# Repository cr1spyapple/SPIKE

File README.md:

# SPIKE
A sleek and speedy ESP32-S3 powered development board

Designed in KiCAD as part of STASIS for Hack Club. I took up this project to learn more about PCB and MCU design. This acts as a prototype of sorts to my e-Reader project <a href="https://github.com/cr1spyapple/Bebop">"Bebop"</a> which will use similar hardware to this.

## Specs:
- 32 GPIO pins
- 16MB flash
- 8MB PSRAM
- WiFi and Bluetooth connectivity
- USB-C port

## PCB Model

## Schematic

## PCB Traces

## Bill of Materials

|Name                                                                                                       |Purpose                   |Quantity|Total Cost (USD)|Link                                                                                                         |Distributor|
|-----------------------------------------------------------------------------------------------------------|--------------------------|--------|----------------|-------------------------------------------------------------------------------------------------------------|-----------|
|10kΩ ±5% 100mW 0603 Thick Film Resistor                                                                    |                          |100     |0.11            |https://www.lcsc.com/product-detail/C2930027.html                                                            |           |
|1.2pF 50V Ceramic Capacitor C0G 0402                                                                       |                          |50      |1.79            |https://www.lcsc.com/product-detail/C76899.html                                                              |           |
|100nF ±10% 16V Ceramic Capacitor X7R 0402                                                                  |                          |100     |0.16            |https://www.lcsc.com/product-detail/C60474.html                                                              |           |
|1uF ±10% 16V Ceramic Capacitor X5R 0402                                                                    |                          |100     |0.38            |https://www.lcsc.com/product-detail/C29266.html                                                              |           |
|20pF ±5% 50V Ceramic Capacitor C0G 0402                                                                    |                          |100     |0.57            |https://www.lcsc.com/product-detail/C76959.html                                                              |           |
|2.7V~3.6V 128Mbit 133MHz SPI SOIC-8-208mil Memory (ICs) RoHS                                               |                          |3       |7.92            |https://www.lcsc.com/product-detail/C97521.html                                                              |           |
|2A 1uH ±20% 95mΩ 3.1A 0805 Fixed Inductors RoHS                                                            |                          |5       |1.05            |https://www.lcsc.com/product-detail/C1331798.html                                                            |           |
|140mA 24nH ±3% 2.3Ω Thick Film Inductor 0201 Fixed Inductors RoHS                                          |                          |100     |0.84            |https://www.lcsc.com/product-detail/C206441.html                                                             |           |
|500mA 2nH 100mΩ 0603 Fixed Inductors RoHS                                                                  |                          |50      |0.65            |https://www.lcsc.com/product-detail/C395081.html                                                             |           |
|USB-C (USB TYPE-C) Receptacle Connector 16 Position Surface Mount                                          |                          |5       |0.94            |https://www.lcsc.com/product-detail/C165948.html                                                             |           |
|Red 645nm LED Indication - Discrete 2.4V 0603                                                              |                          |100     |0.70            |https://www.lcsc.com/product-detail/C2286.html                                                               |           |
|22uF ±20% 10V Ceramic Capacitor X5R 0603                                                                   |                          |10      |0.21            |https://www.lcsc.com/product-detail/C86295.html                                                              |           |
|10nF ±10% 50V Ceramic Capacitor X7R 0603                                                                   |                          |100     |0.37            |https://www.lcsc.com/product-detail/C100042.html                                                             |           |
|499Ω ±1% 62.5mW 0402 Thick Film Resistor                                                                   |                          |100     |0.07            |https://www.lcsc.com/product-detail/C4125.html                                                               |           |
|800mA 2.4nH 80mΩ Multilayer inductor 0402 Fixed Inductors RoHS                                             |                          |10      |0.10            |https://www.lcsc.com/product-detail/C275281.html                                                             |           |
|10uF ±20% 25V Ceramic Capacitor X5R 0603                                                                   |                          |20      |0.61            |https://www.lcsc.com/product-detail/C96446.html                                                              |           |
|Crystal 40MHz ±10ppm 15pF SMD3225-4P                                                                       |                          |10      |0.69            |https://www.lcsc.com/product-detail/C5444549.html                                                            |           |
|SOP-8L Memory (ICs) RoHS                                                                                   |                          |2       |8.93            |https://www.lcsc.com/product-detail/C3028887.html                                                            |           |
|1.5MHz Step-down type Adjustable 600mV~5.5V 2A SOT-563 Voltage Regulators - DC DC Switching Regulators RoHS|                          |5       |0.59            |https://www.lcsc.com/product-detail/C163217.html                                                             |           |
|-98.4dBm 150Mbps 2.412GHz~2.484GHz 2.4GHz 3V~3.6V QFN-56-EP(7x7) RF Transceiver ICs RoHS                   |                          |3       |9.06            |https://www.lcsc.com/product-detail/C2913192.html                                                            |           |
|Tactile Switch SPST 160gf 2mm SMD (SMT) Tab 4mm x 3mm Surface Mount                                        |                          |10      |0.57            |https://www.lcsc.com/product-detail/C720477.html                                                             |           |
|100mW 100kΩ 75V Thick Film Resistor ±100ppm/℃ ±1% 0603 Chip Resistor - Surface Mount RoHS                  |                          |100     |0.15            |https://www.lcsc.com/product-detail/C14675.html                                                              |           |
|453kΩ ±0.1% 100mW 0603 Thin Film Resistor                                                                  |                          |20      |0.48            |https://www.lcsc.com/product-detail/C2686428.html                                                            |           |
|75Ω ±1% 100mW 0603 Thick Film Resistor                                                                     |                          |100     |0.19            |https://www.lcsc.com/product-detail/C4275.html                                                               |           |
|22Ω ±5% 100mW 0603 Thick Film Resistor                                                                     |                          |100     |0.12            |https://www.lcsc.com/product-detail/C2907129.html                                                            |           |
|5.1kΩ ±1% 100mW 0603 Thick Film Resistor                                                                   |                          |100     |0.13            |https://www.lcsc.com/product-detail/C2907044.html                                                            |           |
|0Ω 125mW 200V Thick Film Resistor 0805 Chip Resistor - Surface Mount RoHS                                  |                          |100     |0.63            |https://www.lcsc.com/product-detail/C844934.html                                                             |           |
|4.7uF ±10% 16V Ceramic Capacitor X5R 0603                                                                  |                          |10      |0.14            |https://www.lcsc.com/product-detail/C19666.html                                                              |           |
|Header pins                                                                                                |Header pins for PCB       |1       |1.98            |https://www.aliexpress.com/item/1005008703085861.html?search_p4p_id=202605091107184238603551627500001818552_9|Aliexpress |
|Soldering paste (20g)                                                                                      |Soldering components      |1       |3.46            |https://www.aliexpress.com/item/1005009377104599.html?mp=1                                                   |Aliexpress |
|Hot Plate                                                                                                  |Soldering SMD components  |1       |13.99           |https://www.aliexpress.com/item/1005007016135854.html?mp=1                                                   |Aliexpress |
|65W Type-C power adapter                                                                                   |Power supply for Hot Plate|1       |12.68           |https://www.ebay.co.uk/itm/406309629830                                                                      |Ebay       |
|PCB                                                                                                        |PCB                       |5       |4.10            |                                                                                                             |JLCPCB     |

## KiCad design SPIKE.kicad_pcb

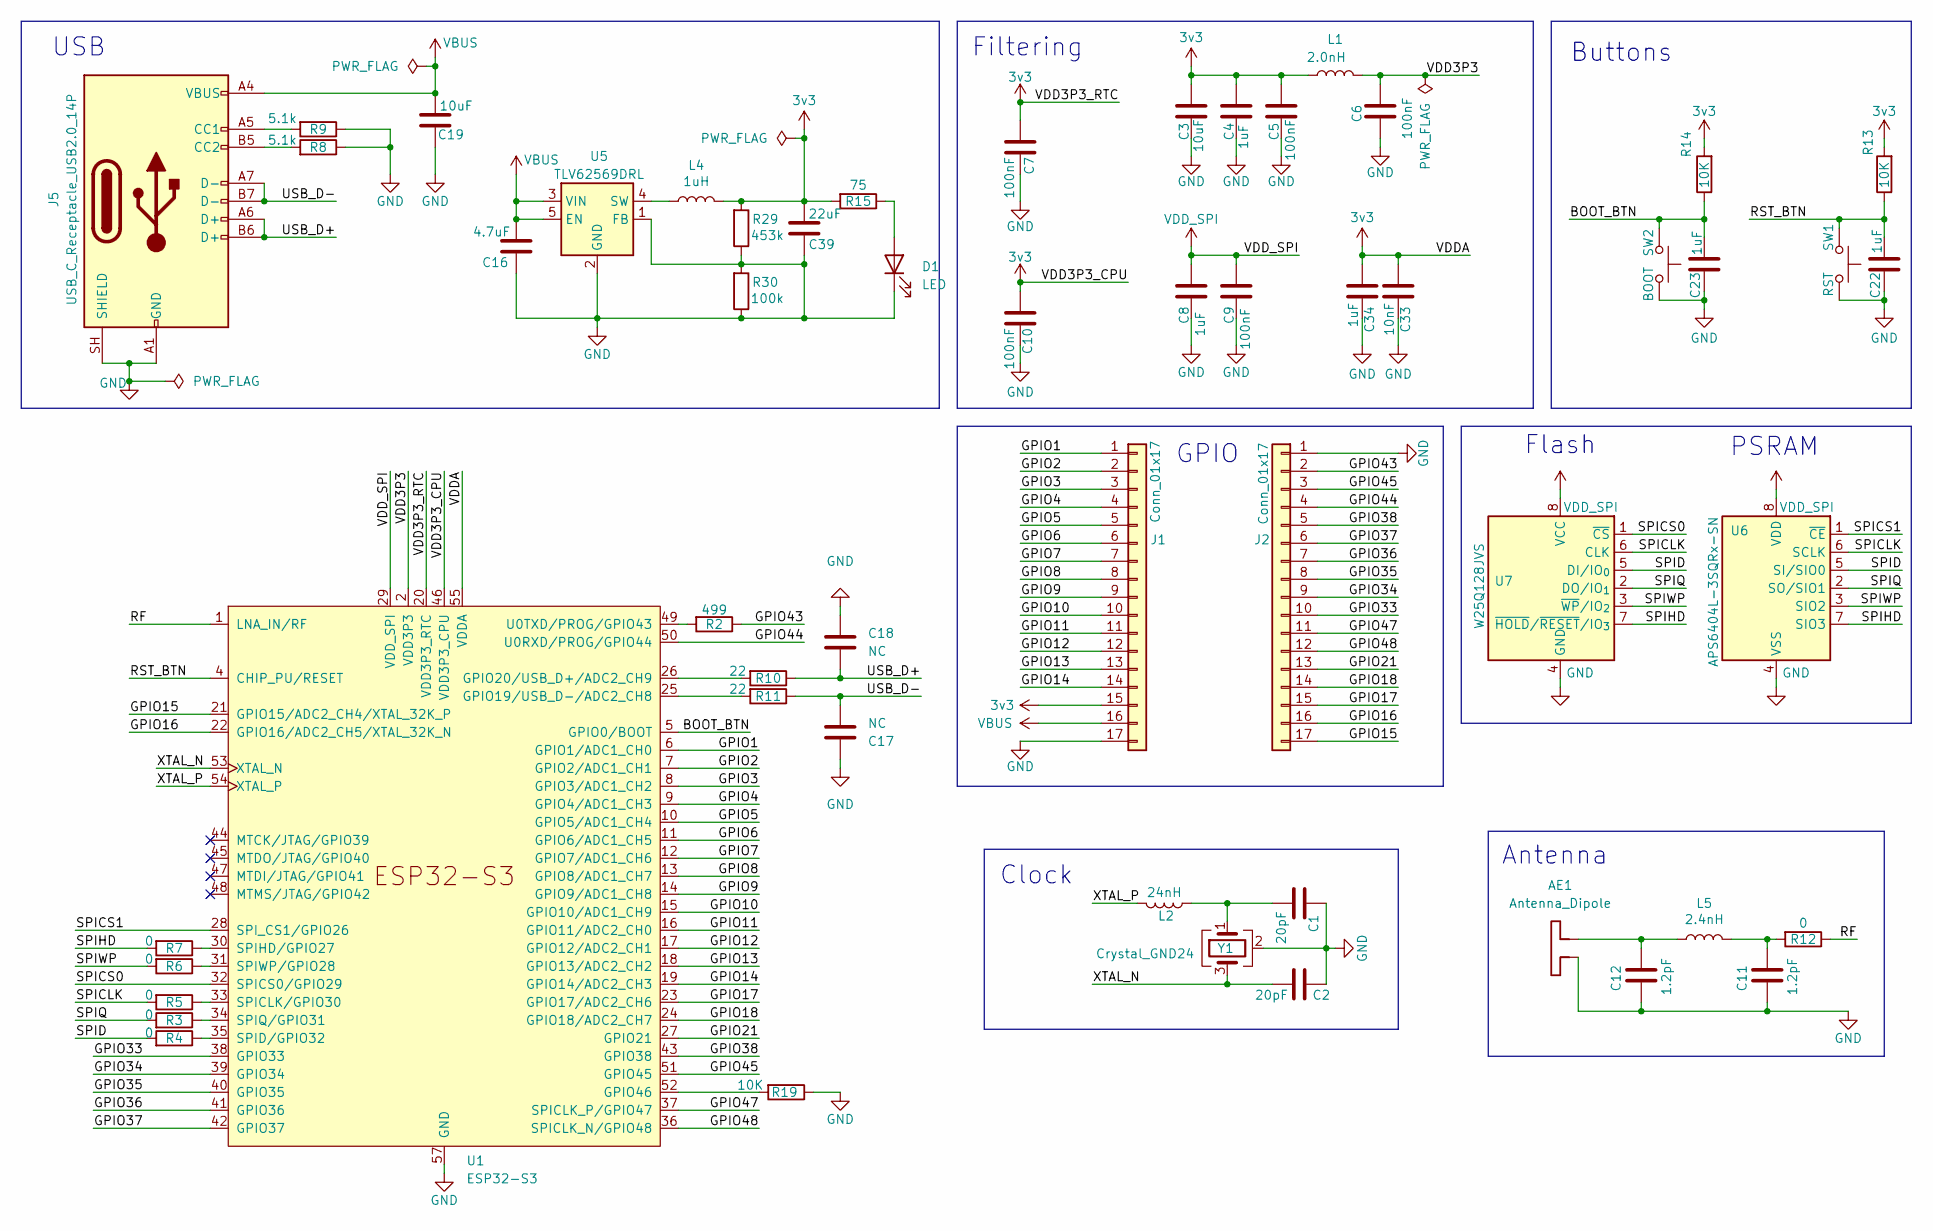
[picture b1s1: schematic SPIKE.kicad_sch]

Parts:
AE1: Antenna_Dipole; Trace Antenna 2.4GHz
C1, C2: 20pF; C_0402_1005Metric; MNF PART NUMBER C1554
C3, C19: 10uF; C_0603_1608Metric; MNF PART NUMBER C19702
C4, C8, C22, C23, C34: 1uF; C_0402_1005Metric; MNF PART NUMBER C52923
C5, C6, C7, C9, C10: 100nF; C_0402_1005Metric; MNF PART NUMBER C1591
C11, C12: 1.2pF; C_0402_1005Metric; MNF PART NUMBER C52923
C16: 4.7uF; C_0603_1608Metric; MNF PART NUMBER C19702
C17, C18: NC; R_0805_2012Metric
C33: 10nF; C_0603_1608Metric; MNF PART NUMBER C57112
C39: 22uF; C_0603_1608Metric; MNF PART NUMBER C19702
D1: LED; LED_0603_1608Metric; MFN PART NUMBER C2286
J1, J2: Conn_01x17; PinHeader_1x17_P2.54mm_Vertical
J5: USB_C_Receptacle_USB2.0_14P; USB_C_Receptacle_HRO_TYPE-C-31-M-12; MNF PART NUMBER C165948
L1: 2.0nH; L_0603_1608Metric; MNF PART NUMBER C370234
L2: 24nH; L_0201_0603Metric; MNF PART NUMBER C139271
L4: 1uH; L_0805_2012Metric; MNF PART NUMBER C19533
L5: 2.4nH; L_0805_2012Metric; MNF PART NUMBER C19533
R2: 499; R_0805_2012Metric; MNF PART NUMBER C17722
R3, R4, R5, R6, R7, R12: 0; R_0805_2012Metric; MNF PART NUMBER C17477
R8, R9: 5.1k; R_0603_1608Metric; MNF PART NUMBER C23186
R10, R11: 22; R_0603_1608Metric; MNF PART NUMBER C23345
R13, R14, R19: 10K; R_0603_1608Metric; MNF PART NUMBER C25804
R15: 75; R_0603_1608Metric; MNF PART NUMBER C4275
R29: 453k; R_0603_1608Metric; MNF PART NUMBER C101055
R30: 100k; R_0603_1608Metric; MNF PART NUMBER C25803
SW1: RST; SW_Push_SPST_NO_Alps_SKRK; MNF PART NUMBER C720477
SW2: BOOT; SW_Push_SPST_NO_Alps_SKRK; MNF PART NUMBER C720477
U1: ESP32-S3; QFN-56-1EP_7x7mm_P0.4mm_EP5.6x5.6mm; MNF PART NUMBER C2913192
U5: TLV62569DRL; SOT-563; MNF PART NUMBER C163217
U6: APS6404L-3SQRx-SN; SOIC-8_3.9x4.9mm_P1.27mm; MNF PART NUMBER C5333729
U7: W25Q128JVS; SOIC-8_5.3x5.3mm_P1.27mm; MNF PART NUMBER C97521
Y1: Crystal_GND24; Crystal_SMD_3225-4Pin_3.2x2.5mm; MNF PART NUMBER C9010

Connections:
3v3: C3.2, C4.2, C5.2, C7.2, C10.2, C33.2, C34.2, C39.2, J1.15, L1.1, L4.1, R13.2, R14.2, R15.2, R29.2, U1.20 (VDD3P3_RTC), U1.46 (VDD3P3_CPU), U1.55 (VDDA), U1.56 (VDDA)
/BOOT_BTN: C23.2, R14.1, SW2.1, U1.5 (GPIO0/BOOT)
/GPIO1: J1.1, U1.6 (GPIO1/ADC1_CH0)
/GPIO2: J1.2, U1.7 (GPIO2/ADC1_CH1)
/GPIO3: J1.3, U1.8 (GPIO3/ADC1_CH2)
/GPIO4: J1.4, U1.9 (GPIO4/ADC1_CH3)
/GPIO5: J1.5, U1.10 (GPIO5/ADC1_CH4)
/GPIO6: J1.6, U1.11 (GPIO6/ADC1_CH5)
/GPIO7: J1.7, U1.12 (GPIO7/ADC1_CH6)
/GPIO8: J1.8, U1.13 (GPIO8/ADC1_CH7)
/GPIO9: J1.9, U1.14 (GPIO9/ADC1_CH8)
/GPIO10: J1.10, U1.15 (GPIO10/ADC1_CH9)
/GPIO11: J1.11, U1.16 (GPIO11/ADC2_CH0)
/GPIO12: J1.12, U1.17 (GPIO12/ADC2_CH1)
/GPIO13: J1.13, U1.18 (GPIO13/ADC2_CH2)
/GPIO14: J1.14, U1.19 (GPIO14/ADC2_CH3)
/GPIO15: J2.17, U1.21 (GPIO15/ADC2_CH4/XTAL_32K_P)
/GPIO16: J2.16, U1.22 (GPIO16/ADC2_CH5/XTAL_32K_N)
/GPIO17: J2.15, U1.23 (GPIO17/ADC2_CH6)
/GPIO18: J2.14, U1.24 (GPIO18/ADC2_CH7)
/GPIO21: J2.13, U1.27 (GPIO21)
/GPIO33: J2.10, U1.38 (GPIO33)
/GPIO34: J2.9, U1.39 (GPIO34)
/GPIO35: J2.8, U1.40 (GPIO35)
/GPIO36: J2.7, U1.41 (GPIO36)
/GPIO37: J2.6, U1.42 (GPIO37)
/GPIO38: J2.5, U1.43 (GPIO38)
/GPIO43: J2.2, R2.1
/GPIO44: J2.4, U1.50 (U0RXD/PROG/GPIO44)
/GPIO45: J2.3, U1.51 (GPIO45)
/GPIO47: J2.11, U1.37 (SPICLK_P/GPIO47)
/GPIO48: J2.12, U1.36 (SPICLK_N/GPIO48)
/RF: R12.1, U1.1 (LNA_IN/RF)
/RST_BTN: C22.2, R13.1, SW1.1, U1.4 (CHIP_PU/RESET)
/SPICLK: R5.2, U6.6 (SCLK), U7.6 (CLK)
/SPICS0: U1.32 (SPICS0/GPIO29), U7.1 (~CS)
/SPICS1: U1.28 (SPI_CS1/GPIO26), U6.1 (~CE)
/SPID: R4.2, U6.5 (SI/SIO0), U7.5 (DI/IO_{0})
/SPIHD: R7.2, U6.7 (SIO3), U7.7 (~HOLD/~RESET/IO_{3})
/SPIQ: R3.2, U6.2 (SO/SIO1), U7.2 (DO/IO_{1})
/SPIWP: R6.2, U6.3 (SIO2), U7.3 (~WP/IO_{2})
/USB_D+: C18.2, J5.A6 (D+), J5.B6 (D+), R10.1
/USB_D-: C17.2, J5.A7 (D-), J5.B7 (D-), R11.1
/XTAL_N: C2.2, U1.53 (XTAL_N), Y1.3
/XTAL_P: L2.2, U1.54 (XTAL_P)
GND: AE1.1, C1.1, C2.1, C3.1, C4.1, C5.1, C6.1, C7.1, C8.1, C9.1, C10.1, C11.1, C12.1, C16.1, C17.1, C18.1, C19.1, C22.1, C23.1, C33.1, C34.1, C39.1, D1.1 (K), J1.17, J2.1, J5.A1 (GND), J5.A12 (GND), J5.B1 (GND), J5.B12 (GND), J5.SH (SHIELD), R8.1, R9.1, R19.1, R29.1, R30.1, R30.2, SW1.2, SW2.2, U1.57 (GND), U5.1 (FB), U5.2 (GND), U6.4 (VSS), U7.4 (GND), Y1.2 (G), Y1.4 (G)
unnamed: AE1.2, C12.2, L5.2
unnamed: C1.2, L2.1, Y1.1
unnamed: C11.2, L5.1, R12.2
unnamed: D1.2 (A), R15.1
unnamed: J5.A5 (CC1), R9.2
unnamed: J5.B5 (CC2), R8.2
unnamed: R11.2, U1.25 (GPIO19/USB_D-/ADC2_CH8)
unnamed: R10.2, U1.26 (GPIO20/USB_D+/ADC2_CH9)
unnamed: R19.2, U1.52 (GPIO46)
unnamed: R5.1, U1.33 (SPICLK/GPIO30)
unnamed: R4.1, U1.35 (SPID/GPIO32)
unnamed: R7.1, U1.30 (SPIHD/GPIO27)
unnamed: R3.1, U1.34 (SPIQ/GPIO31)
unnamed: R6.1, U1.31 (SPIWP/GPIO28)
unnamed: R2.2, U1.49 (U0TXD/PROG/GPIO43)
unnamed: L4.2, U5.4 (SW)
VBUS: C16.2, C19.2, J1.16, J5.A4 (VBUS), J5.A9 (VBUS), J5.B4 (VBUS), J5.B9 (VBUS), U5.3 (VIN), U5.5 (EN)
VDD3P3: C6.2, L1.2, U1.2 (VDD3P3), U1.3 (VDD3P3)
VDD_SPI: C8.2, C9.2, U1.29 (VDD_SPI), U6.8 (VDD), U7.8 (VCC)

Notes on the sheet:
Flash
USB
Clock
Antenna
GPIO
Filtering
PSRAM
Buttons

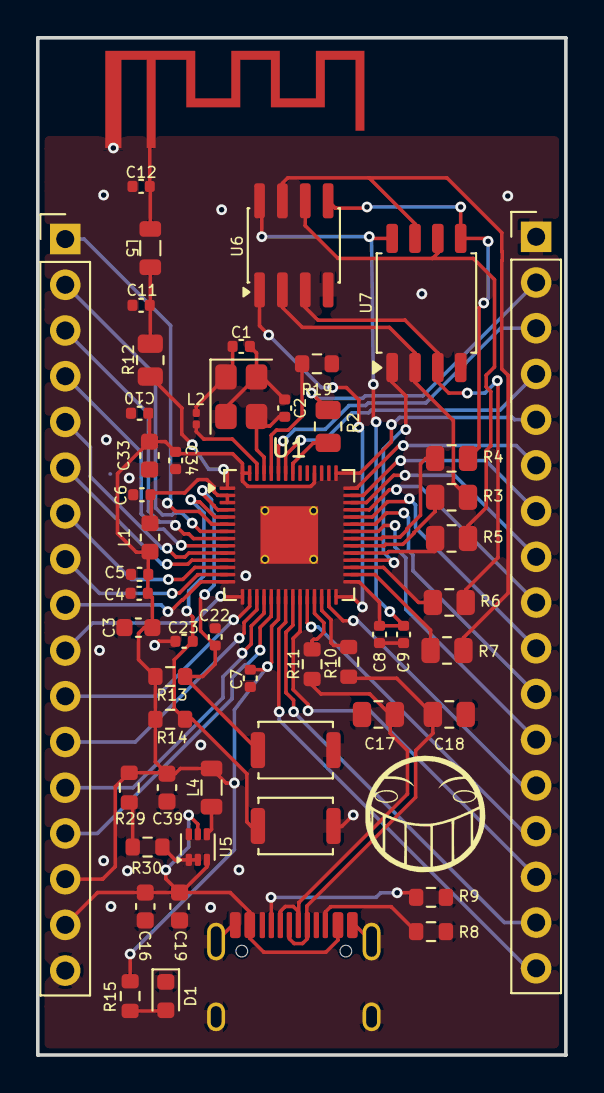
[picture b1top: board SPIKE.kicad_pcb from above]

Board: 2 copper layers, 29.3 x 56.5 mm, 56 parts (1 on the bottom side), 65 nets.

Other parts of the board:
Back: LOGO; Spike_manga
Front: LOGO; ED_smile

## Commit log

2026-05-08 Move 1778265195.png to Pics/1778265195.png
2026-05-08 Move 1778265259.png to Pics/Back_Trace.png
2026-05-08 Rename 1778265195.png to Front_Trace.png
2026-05-09 Upload gerbers and some modifications
2026-05-15 Added bill of materials
2026-06-09 Rename production/SPIKE-bom.csv to SPIKE-bom.csv
